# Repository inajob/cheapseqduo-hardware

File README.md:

# これはなに？

勢いで作った基板です。

CheapSeqDuo

- Arduino Nanoを2つ搭載し
- ピアノ風のキーボード
- OLED(128x64または128x32）
- 単4電池x4本
- オーディオジャック
- ボリューム
- 10cm x 10cm

1つのArduinoをコントローラに、もう一つのArduinoを音源用に、と思い配置しています。

# TODO

- ファームウェアがまだない（一応自分の作った物を近いうちに公開しますが、大したものではないのでそれぞれ作るのが良いと思います）
- BOMがない

# 既知のバグ

- 2つのArduinoのTX,RXが直結されているので、2つ基板に配置するとArduinoとして書き込みできない（致命的）
  - パターンカットしてスイッチでTX,RXを繋げるようにするのがよさそう
- D13にLEDがついている関係でキースキャンがうまくできない、プルアップ抵抗を入れる事で回避できる
- (仕様) オーディオジャック、ボリュームのフットプリントはあるが未接続です。自分で手配線してArduinoと接続したり、オーディオアンプを構成したりしてください。

# 感謝

この基板はALLPCBのキャンペーンで無料で基板が作れるという事で作り始めたものです。

下記リンクからALLPCBを初めて利用すると、$30のクーポンがもらえますのでどうぞ。

[クーポン付きALLPCB入会URL](https://www.allpcb.com/?Mb_InviteId=77225)

(2021年7月現在 ALLPCBは「毎月送料含め基板無料キャンペーン」をやっているようで、この基板であれば5枚が無料で作れます。

# ライセンス

CC SA-BY とします。

（面白いボードができたら http://twitter.com/ina_ani まで教えてください。余ったら1枚ください！動くものが出来た場合はどこかで遊ばせてほしいです！）

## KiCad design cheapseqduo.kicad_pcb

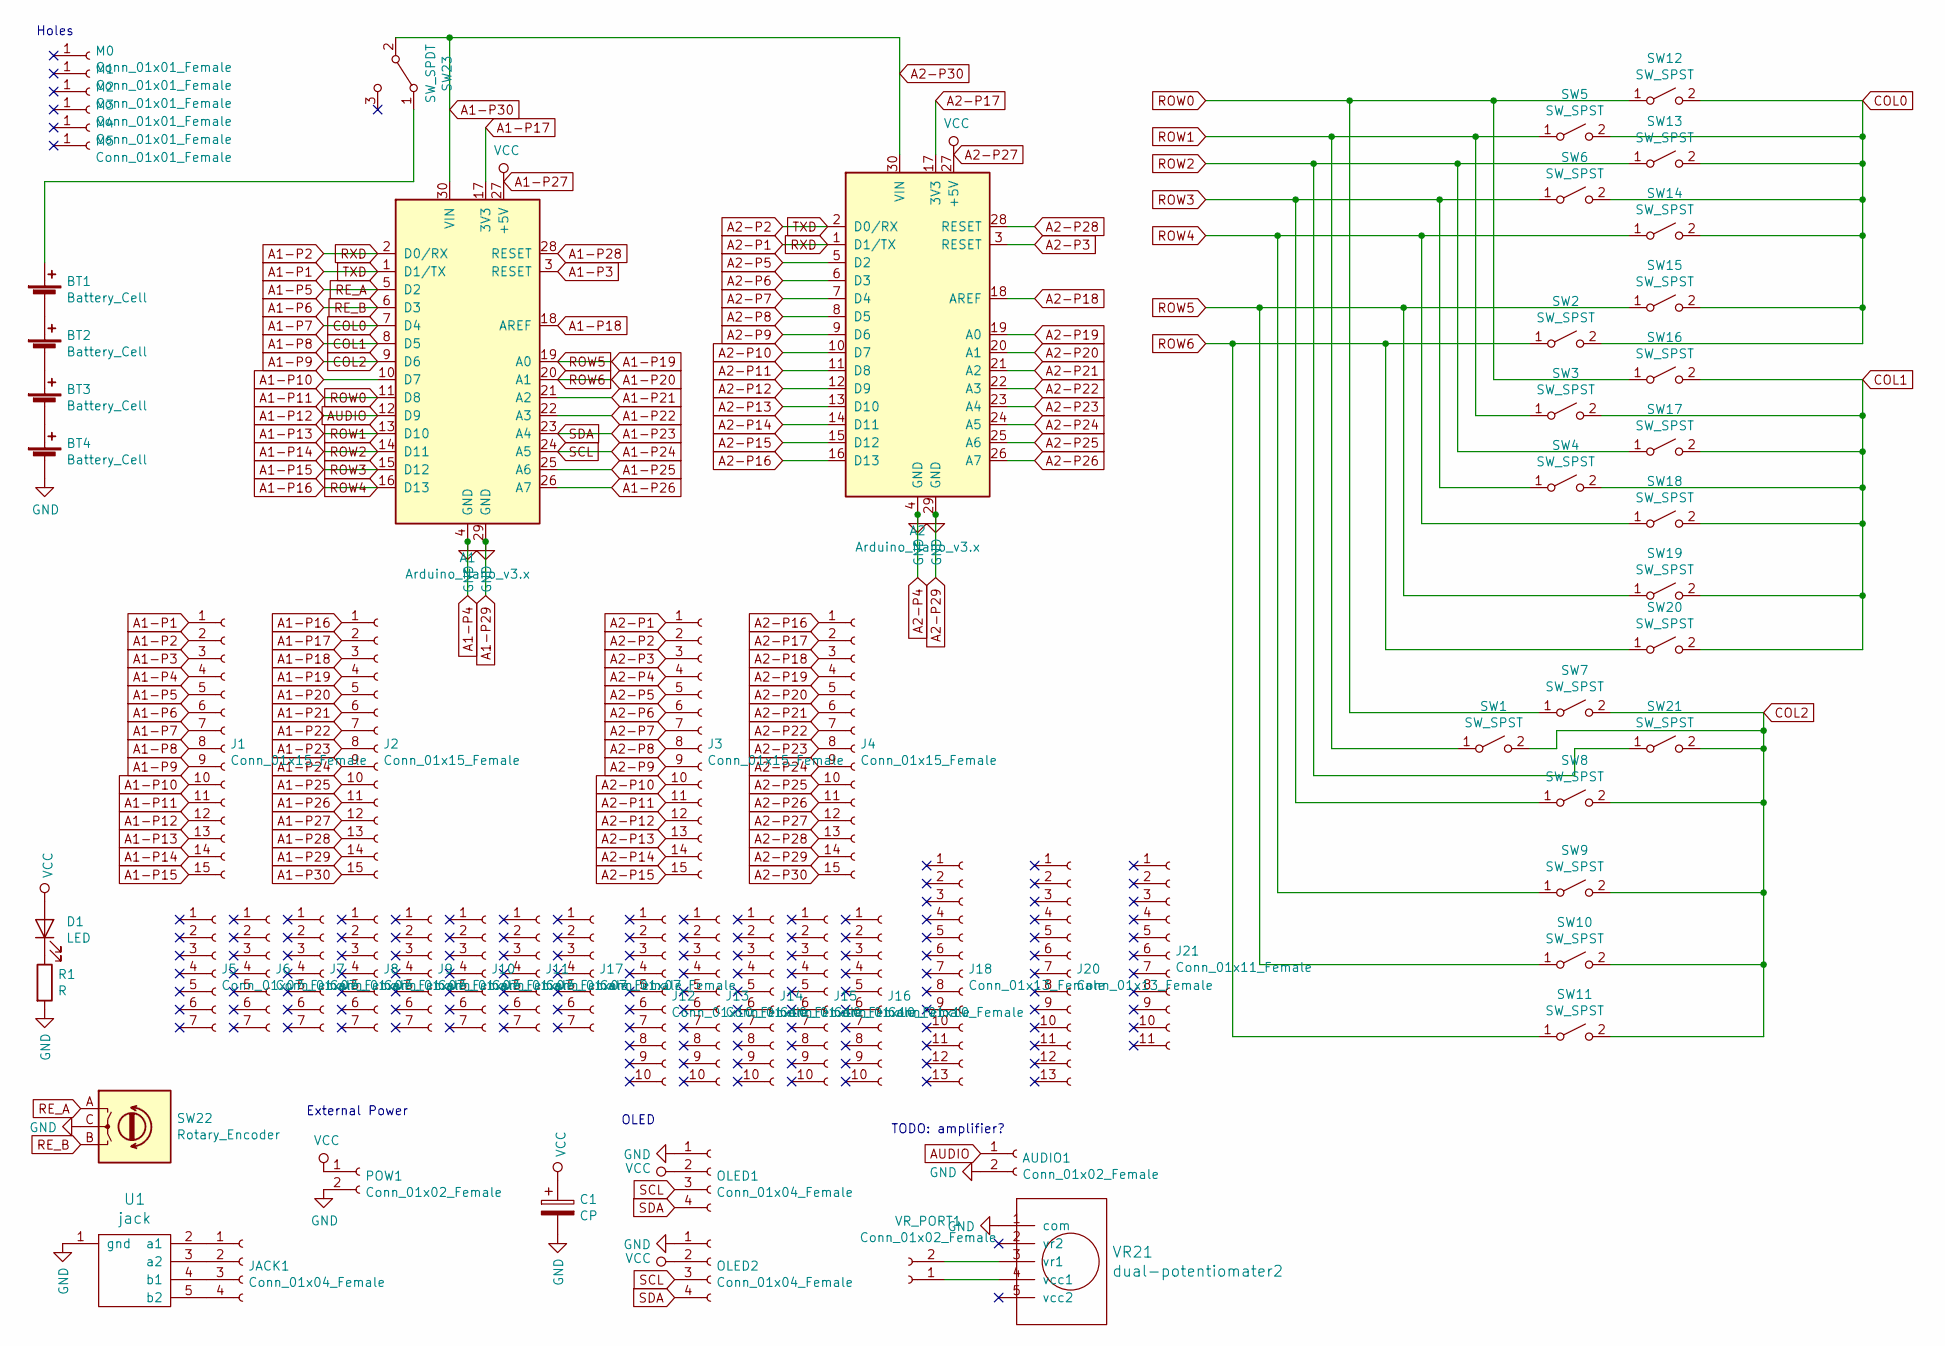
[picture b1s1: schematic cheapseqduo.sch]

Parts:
A1, A2: Arduino_Nano_v3.x; Arduino_Nano
AUDIO1: Conn_01x02_Female; PinHeader_2x01_P2.54mm_Vertical
BT1, BT2, BT3, BT4: Battery_Cell; BatteryHolder_Keystone_2466_1xAAA
C1: CP; CP_Radial_D6.3mm_P2.50mm
D1: LED; LED_D4.0mm
J1, J2, J3, J4: Conn_01x15_Female; PinHeader_1x15_P2.54mm_Vertical
J5, J6, J7, J8, J9, J10, J11, J17: Conn_01x07_Female; PinHeader_1x07_P2.54mm_Vertical
J12, J13, J14, J15, J16: Conn_01x10_Female; PinHeader_1x10_P2.54mm_Vertical
J18, J20: Conn_01x13_Female; PinHeader_1x13_P2.54mm_Vertical
J21: Conn_01x11_Female; PinHeader_1x11_P2.54mm_Vertical
JACK1: Conn_01x04_Female; PinHeader_1x04_P2.54mm_Vertical
M0, M1, M2, M3, M4, M5: Conn_01x01_Female; MountingHole_3.2mm_M3
OLED1, OLED2: Conn_01x04_Female; PinHeader_1x04_P2.54mm_Vertical
POW1: Conn_01x02_Female; PinHeader_1x02_P2.54mm_Vertical
R1: R; R_Axial_DIN0207_L6.3mm_D2.5mm_P7.62mm_Horizontal
SW1, SW2, SW3, SW4, SW5, SW6, SW7, SW8, SW9, SW10, SW11, SW12, SW13, SW14, SW15, SW16, SW17, SW18, SW19, SW20, SW21: SW_SPST; SW_PUSH_6mm_H8mm
SW22: Rotary_Encoder; RotaryEncoder_Alps_EC12E_Vertical_H20mm_CircularMountingHol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
SW23: SW_SPDT; PinHeader_1x03_P2.54mm_Vertical
U1: jack
VR21: dual-potentiomater2; potentiometer2
VR_PORT1: Conn_01x02_Female; PinHeader_1x02_P2.54mm_Vertical

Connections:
A1-P1: A1.1 (D1/TX), A2.2 (D0/RX), J1.1, J3.2
A1-P2: A1.2 (D0/RX), A2.1 (D1/TX), J1.2, J3.1
A1-P3: A1.3 (RESET), J1.3
A1-P5: A1.5 (D2), J1.5, SW22.A
A1-P6: A1.6 (D3), J1.6, SW22.B
A1-P7: A1.7 (D4), J1.7, SW2.2 (B), SW5.2 (B), SW6.2 (B), SW12.2 (B), SW13.2 (B), SW14.2 (B), SW15.2 (B)
A1-P8: A1.8 (D5), J1.8, SW3.2 (B), SW4.2 (B), SW16.2 (B), SW17.2 (B), SW18.2 (B), SW19.2 (B), SW20.2 (B)
A1-P9: A1.9 (D6), J1.9, SW1.2 (B), SW7.2 (B), SW8.2 (B), SW9.2 (B), SW10.2 (B), SW11.2 (B), SW21.2 (B)
A1-P10: A1.10 (D7), J1.10
A1-P11: A1.11 (D8), J1.11, SW7.1 (A), SW12.1 (A), SW16.1 (A)
A1-P12: A1.12 (D9), AUDIO1.1, J1.12
A1-P13: A1.13 (D10), J1.13, SW1.1 (A), SW3.1 (A), SW5.1 (A)
A1-P14: A1.14 (D11), J1.14, SW13.1 (A), SW17.1 (A), SW21.1 (A)
A1-P15: A1.15 (D12), J1.15, SW4.1 (A), SW6.1 (A), SW8.1 (A)
A1-P16: A1.16 (D13), J2.1, SW9.1 (A), SW14.1 (A), SW18.1 (A)
A1-P17: A1.17 (3V3), J2.2
A1-P18: A1.18 (AREF), J2.3
A1-P19: A1.19 (A0), J2.4, SW10.1 (A), SW15.1 (A), SW19.1 (A)
A1-P20: A1.20 (A1), J2.5, SW2.1 (A), SW11.1 (A), SW20.1 (A)
A1-P21: A1.21 (A2), J2.6
A1-P22: A1.22 (A3), J2.7
A1-P23: A1.23 (A4), J2.8, OLED1.4, OLED2.4
A1-P24: A1.24 (A5), J2.9, OLED1.3, OLED2.3
A1-P25: A1.25 (A6), J2.10
A1-P26: A1.26 (A7), J2.11
A1-P27: A1.27 (+5V), A2.27 (+5V), C1.1, D1.2 (A), J2.12, J4.12, OLED1.2, OLED2.2, POW1.1
A1-P28: A1.28 (RESET), J2.13
A1-P29: A1.4 (GND), A1.29 (GND), A2.4 (GND), A2.29 (GND), AUDIO1.2, BT4.2 (-), C1.2, J1.4, J2.14, J3.4, J4.14, OLED1.1, OLED2.1, POW1.2, R1.2, SW22.C, U1.1 (gnd), VR21.1 (com)
A1-P30: A1.30 (VIN), A2.30 (VIN), J2.15, J4.15, SW23.2 (B)
A2-P3: A2.3 (RESET), J3.3
A2-P5: A2.5 (D2), J3.5
A2-P6: A2.6 (D3), J3.6
A2-P7: A2.7 (D4), J3.7
A2-P8: A2.8 (D5), J3.8
A2-P9: A2.9 (D6), J3.9
A2-P10: A2.10 (D7), J3.10
A2-P11: A2.11 (D8), J3.11
A2-P12: A2.12 (D9), J3.12
A2-P13: A2.13 (D10), J3.13
A2-P14: A2.14 (D11), J3.14
A2-P15: A2.15 (D12), J3.15
A2-P16: A2.16 (D13), J4.1
A2-P17: A2.17 (3V3), J4.2
A2-P18: A2.18 (AREF), J4.3
A2-P19: A2.19 (A0), J4.4
A2-P20: A2.20 (A1), J4.5
A2-P21: A2.21 (A2), J4.6
A2-P22: A2.22 (A3), J4.7
A2-P23: A2.23 (A4), J4.8
A2-P24: A2.24 (A5), J4.9
A2-P25: A2.25 (A6), J4.10
A2-P26: A2.26 (A7), J4.11
A2-P28: A2.28 (RESET), J4.13
unnamed: BT1.1 (+), SW23.1 (A)
unnamed: BT1.2 (-), BT2.1 (+)
unnamed: BT2.2 (-), BT3.1 (+)
unnamed: BT3.2 (-), BT4.1 (+)
unnamed: D1.1 (K), R1.1
unnamed: JACK1.1, U1.2 (a1)
unnamed: JACK1.2, U1.3 (a2)
unnamed: JACK1.3, U1.4 (b1)
unnamed: JACK1.4, U1.5 (b2)
unnamed: VR21.3 (vr1), VR_PORT1.2
unnamed: VR21.4 (vcc1), VR_PORT1.1

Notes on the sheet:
TODO: amplifier?
OLED
External Power
Holes

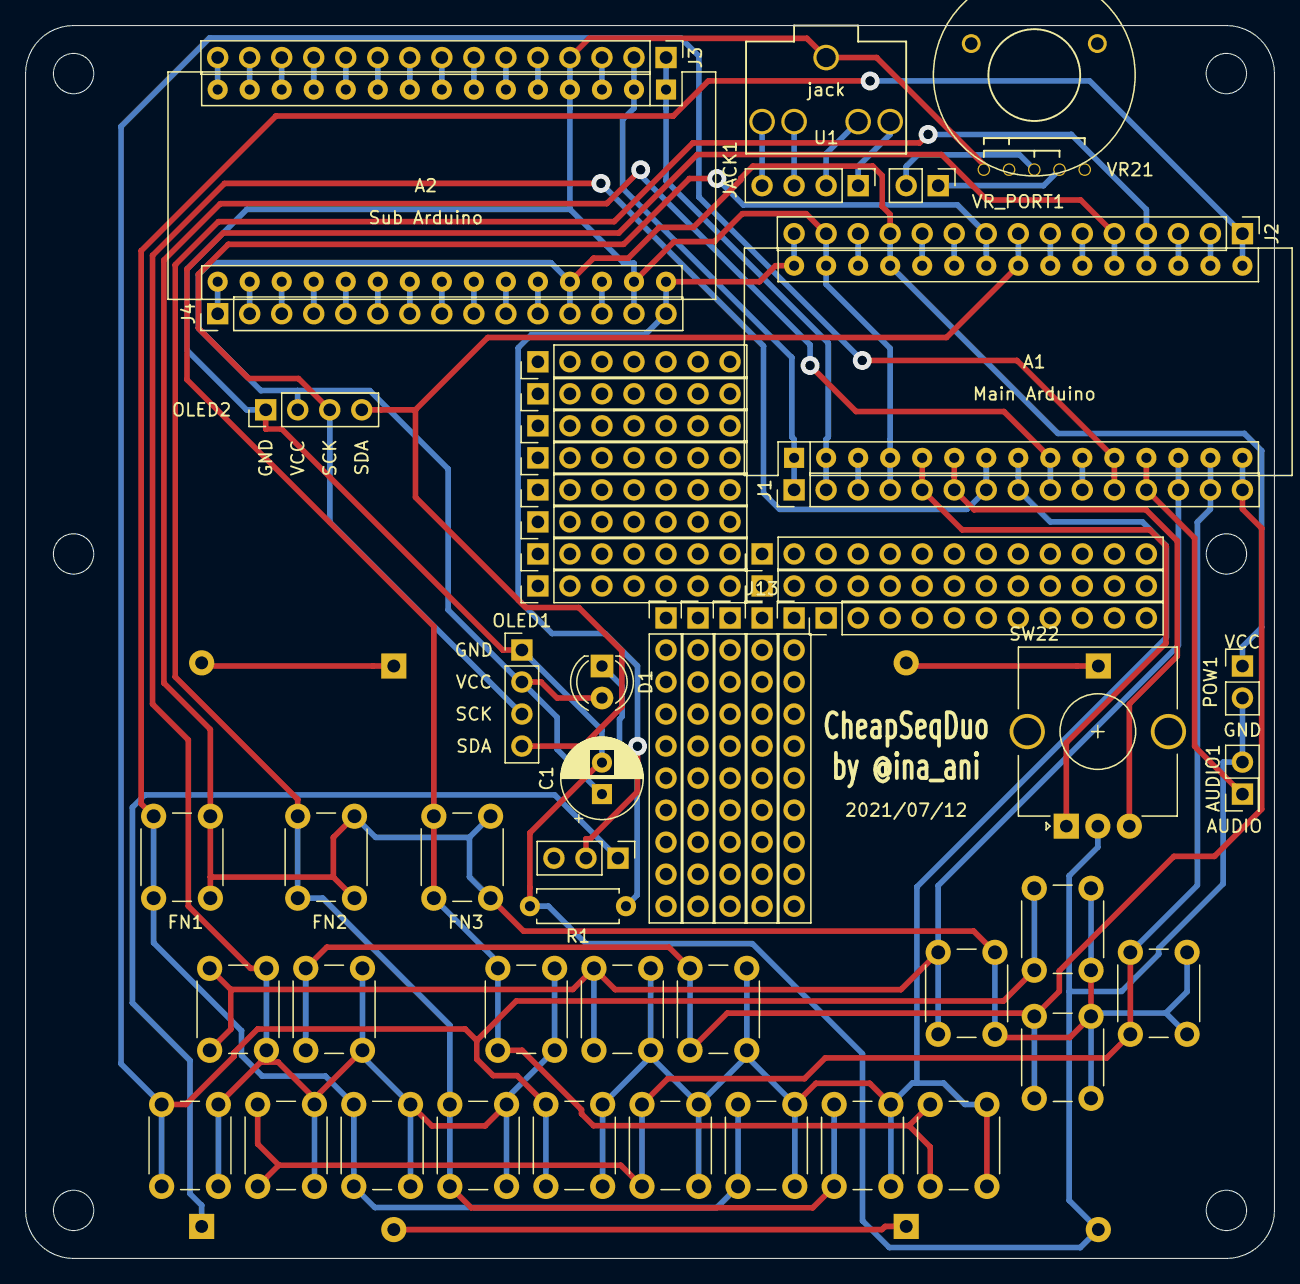
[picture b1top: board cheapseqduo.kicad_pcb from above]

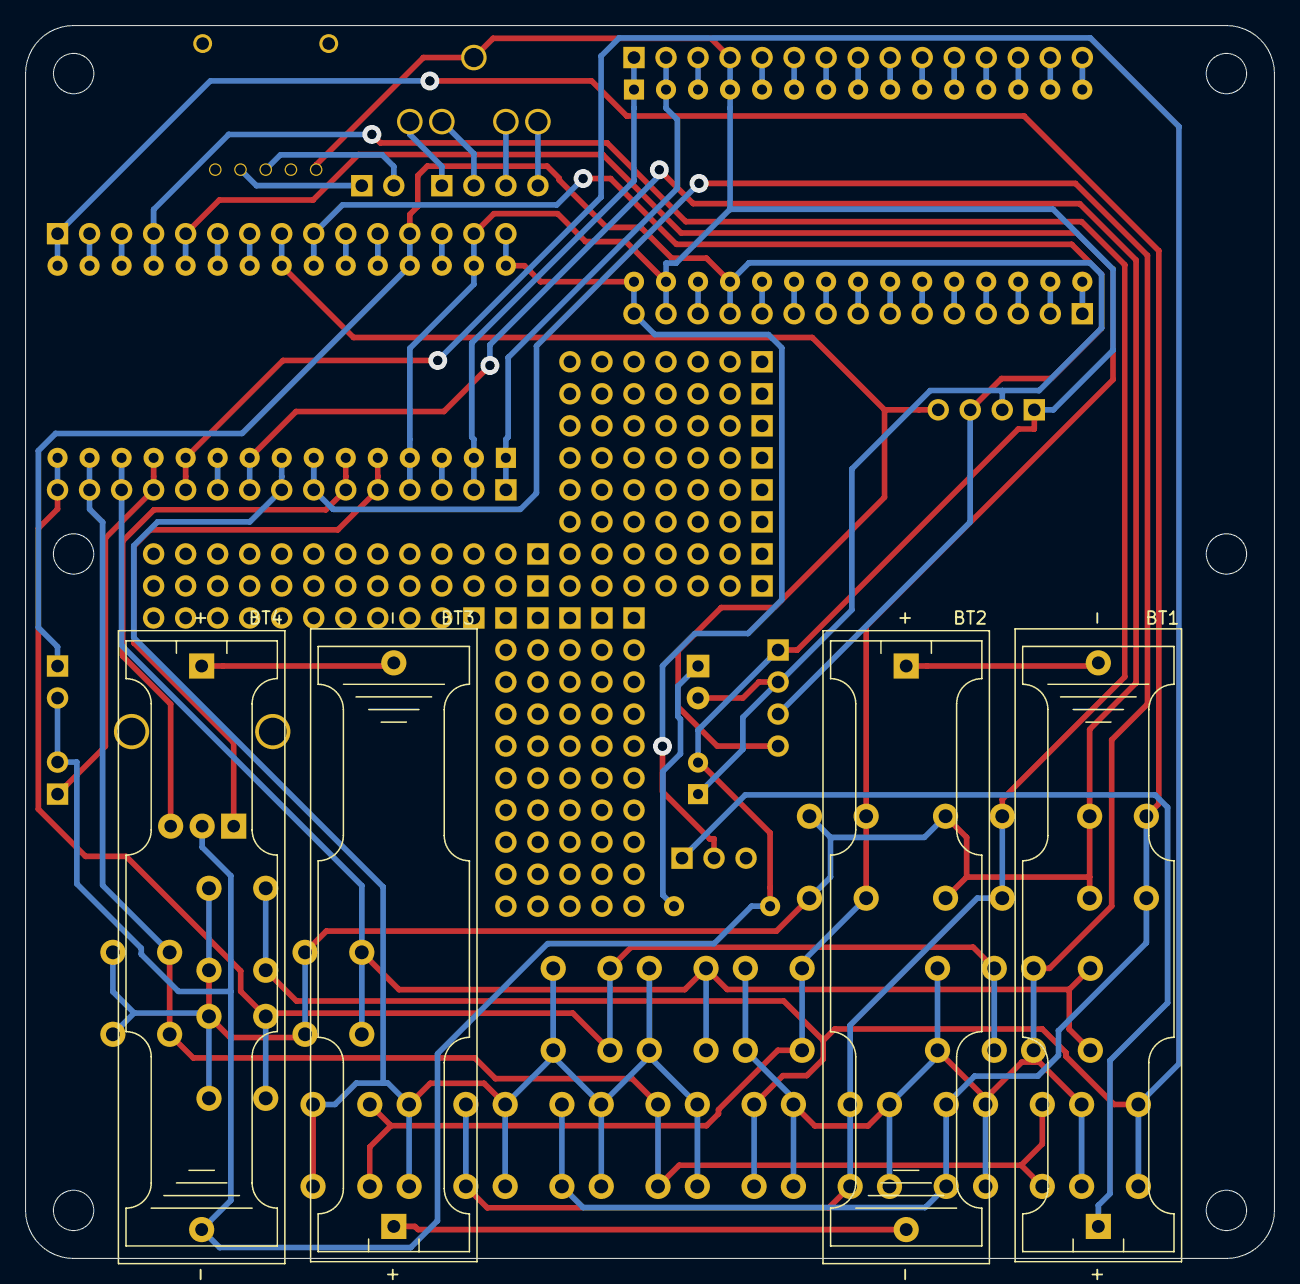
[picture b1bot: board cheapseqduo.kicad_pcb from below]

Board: 2 copper layers, 99.1 x 97.8 mm, 66 parts (4 on the bottom side), 64 nets.

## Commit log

2021-07-27 init
2021-07-27 update link
2021-07-27 add image
2021-07-27 add image file
2021-07-27 add bug list and todo
